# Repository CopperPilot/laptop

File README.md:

# CopperPilot Laptop

**A 13-inch, 13.5 mm thin aluminium laptop built around a Raspberry Pi Compute Module 5, with a 66 Wh 2S battery, 20 V USB-C charging, a scissor keyboard, a glass trackpad and a webcam. Designed end to end by CopperPilot.**

> [!NOTE]
> **Designed by [CopperPilot](https://copperpilot.ai).** CopperPilot's agents designed every board, schematic, layout and enclosure part in this repo from one prompt and a few reference photos, then checked them with the gates and reviews below. Nobody edited the design files by hand: the owner gave plain-English feedback between runs (it is at the end of the prompt), and the agents made every change. **It has not been fabricated, assembled or powered on yet.** Everything here is open for review: if you see something a senior engineer would flag, [open an issue](../../issues/new/choose).

The main board is a carrier for the Compute Module 5 that runs the keyboard, trackpad, display, webcam, speakers,
battery charging and power. Two small daughter boards sit at the edges: two USB-C ports on the left (one is the
20 V charging input) and the headphone jack and microphone on the right. Flat cables join everything, including the
display and webcam cables, which pass through a barrel between the two torque hinges.

## Status

### Done

- [x] Schematic: KiCad ERC, 0 errors
- [x] Layout: KiCad DRC with schematic parity and zone refill, 0 errors, 0 unconnected
- [x] Board rules no looser than the fab's limits, nothing silenced
- [x] Every part on the footprint and 3D model of its exact LCSC part
- [x] Every placed part has a live, in-stock LCSC/JLCPCB part number
- [x] High-speed groups (USB, MIPI, DDR where present) routed, length-matched, on target impedance
- [x] Every user-facing connector opens towards its case opening (checked on its 3D model)
- [x] Every connector mates from a known side, with a keep-clear zone KiCad DRC enforces
- [x] Both ends of every board-to-board cable carry the same signal on each wire
- [x] Datasheet-level design review: 0 P0 and 0 P1 findings open on every board
- [x] Enclosure parts are closed solids that fit the product envelope
- [x] Every enclosure part is manufacturable by its process (wall thickness, build size)
- [x] Full assembly with the real PCBAs: no collisions, seated or along any insertion path
- [x] Every cable joins two real connectors and fits its route in every pose
- [x] Every connector faces what mates with it; every screw hole sits on a boss
- [x] Every port opening has its connector right behind it
- [x] Every button and control physically reaches the switch it works
- [x] Every camera's whole field of view clears the case
- [x] Every part is held by something real (screw, snap, clip, adhesive, press fit)
- [x] Gerbers, drill, BOM and CPL exist and agree with the PCB
- [x] Independent judge (compares renders to the reference photos): **8/10** ([notes](reviews/judge.md))

### Pending

- [ ] Gate `sourcing.bom` warn: 84 extended parts (each adds a JLCPCB feeder fee); prefer basic parts where equivalent
- [ ] Gate `kicad.drc` warn: [main] DRC warning lib_footprint_mismatch x82
- [ ] **Not built.** No board has been fabricated, assembled or powered on, and the enclosure has not been machined.
- [ ] **No software bring-up.** The CM5 device tree, keyboard matrix (TCA8418), trackpad, display panel, webcam and charger settings over I2C are not written or tested.
- [ ] **Bought parts are specified from drawings.** The keyboard, trackpad, 13-inch MIPI panel, hinges, speakers and the custom 2S2P pack are modelled from typical drawings; real suppliers and exact parts still have to be chosen and the models checked against them.
- [ ] **Thermal design not analysed.** No thermal simulation or heat-spreading plan for the CM5 inside the closed aluminium case.
- [ ] **Peak battery current to verify.** Several earlier design reviews estimated that peak load near the 2S cut-off (CM5, display, speakers and USB-C together) can exceed the BQ25798's 6 A internal battery switch; the final review did not raise it. Measure the peak load budget at bring-up, and add an external battery switch or a load cap if it holds.
- [ ] **Thickness:** the assembly measures 13.45 mm against the 12.7 mm target (within the ±1 mm tolerance the design contract allows).
- [ ] **Judge notes (8/10):** separate left and right torque-hinge barrels with a centre cable cover, where the reference has one full-width clutch cover; full-height arrow keys instead of a half-height inverted-T cluster; the webcam window is a rectangular cutout rather than a flush glass hole.
- [ ] **DRC warnings:** 245 across the boards (mostly footprints that differ from their library copy and silkscreen over copper or overlapping); 0 errors.

0 P0 · 0 P1 · 0 P2 review findings open; the full reviews with evidence and suggested fixes are in [reviews/](reviews). Every P0 and P1 the reviews raised was fixed before release.

## Build film

[docs/build-film.mp4](docs/build-film.mp4) (51 s, 720p). Every part backs out along the direction it was fitted and goes back in assembly order, and every cable is drawn along its real route. Every frame is replayed against the 3D models (no part passes through another, the camera stays outside, the product stays in frame and faces you, no flicker), and a separate critic watches the film ([notes](reviews/film.md)).

## Renders

| | |
|:---:|:---:|
| <br>*Three-quarter view* | <br>*Front* |
| <br>*Rear* | <br>*Left side* |
| <br>*Right side* | <br>*Exploded* |
| <br>*Inside, top cover lifted away, every cable* | <br>*Inside from below, bottom cover lifted away* |
| <br>*Ports* | <br>*Buttons and controls, next to the parts they press* |

## What's inside

**Power path:** USB-C PD sink (CH224A, asks for 20 V) → BQ25798 buck-boost charger with NVDC power path → one
2S2P pack of four identical LP4466104 cells (7.4 V, 9 Ah, 66.6 Wh) shaped around the trackpad → two 6 A 5 V bucks
(TPS56628) for the CM5 and the peripherals.

| Board | Size | Layers | Parts | Tracks | Vias | KiCad project | Review |
|---|---|---|---|---|---|---|---|
| Main board | 160 × 44 mm | 4 | 285 | 5,693 | 856 | [`hardware/thin-laptop-cm5.kicad_pro`](hardware/thin-laptop-cm5.kicad_pro) | [0 P0 · 0 P1](reviews/review-main.md) |
| Left Dual USB-C PD & Data Daughter Board | 36 × 38 mm | 4 | 67 | 1,218 | 93 | [`hardware/usb_left/thin-laptop-cm5-usb_left.kicad_pro`](hardware/usb_left/thin-laptop-cm5-usb_left.kicad_pro) | [0 P0 · 0 P1](reviews/review-usb_left.md) |
| Right Headphone & Microphone Daughter Board | 36 × 38 mm | 2 | 74 | 555 | 84 | [`hardware/audio_right/thin-laptop-cm5-audio_right.kicad_pro`](hardware/audio_right/thin-laptop-cm5-audio_right.kicad_pro) | [0 P0 · 0 P1](reviews/review-audio_right.md) |

**Bought parts** (modelled from their drawings; the assembly checks use these models):

- **Cm5 module**: Raspberry Pi Compute Module 5 (BCM2712 quad-core Cortex-A76, 8GB LPDDR4X, 64GB eMMC, Wi-Fi/BLE)
- **Keyboard module**: 78-key ANSI ultra-thin scissor-switch laptop keyboard module with printed legends and 24-pin 0.5mm FPC tail
- **Trackpad module**: Capacitive multi-touch glass-surface I2C laptop trackpad module with 8-pin 0.5mm FPC tail
- **Display panel**: 13.0-inch 2560x1600 4-lane MIPI DSI IPS thin LCD panel with integrated WLED backlight bar
- **Webcam module**: Slim 1080p MIPI CSI-2 camera module with 22-pin 0.5mm micro-coax receptacle for laptop top bezel
- **Battery pack**: Custom 2S2P 7.4V nominal
- **Speaker left**: Low-profile 8-ohm 2W rectangular laptop speaker box module (left channel)
- **Speaker right**: Low-profile 8-ohm 2W rectangular laptop speaker box module (right channel)
- **Hinge left**: Compact friction torque laptop hinge (left)
- **Hinge right**: Compact friction torque laptop hinge (right)

## How it was made

CopperPilot's agents worked from the prompt in [reference/prompt.md](reference/prompt.md) and 6 reference photos ([reference/](reference)). The pipeline scopes the product into a written contract ([design/spec.yaml](design/spec.yaml)), designs the boards and the enclosure in parallel, integrates them, and only moves on when the gates pass. A separate review agent reads every board against the part datasheets, and a separate judge compares the result with the photos.

- Pipeline wall clock: about **136 h** over 25 launches (pipeline v68 to v127).

**Reference vs build:**

<sub>Reference photos of a commercial product, used here only for comparison. All rights belong to their owners; this project is not affiliated with or endorsed by the product's maker.</sub>

## Repository layout

```
hardware/          KiCad 10 projects (main board at the top, daughter boards in their own folders)
  lcsc.*, rea_refs.*   symbols, footprints and 3D models for every part, so the project opens anywhere
case/out/          enclosure parts (STL)
case/purchased/    bought parts used in the assembly checks
case/generate_case.py  the parametric enclosure source (uses CopperPilot's CAD helpers, not yet public)
fab/               Gerbers, drill, BOM, CPL, schematic PDF and STEP for each board; fab/mech/ enclosure STEP/STL
design/spec.yaml   the design contract the agents wrote and the gates check
reviews/           gate report, design reviews, the judge's notes, KiCad ERC/DRC
reference/         the prompt and the reference photos
docs/              build film and renders
```

## Manufacture

Every board targets **JLCPCB** standard PCB + assembly (1.6 mm FR-4); every part has an LCSC number. Per board: upload `*-gerbers.zip`, then `*-bom.csv` and `*-cpl.csv` for assembly, and check the part rotations in JLCPCB's preview before ordering.

The enclosure (`fab/mech/`) is designed for CNC-machined 6061 aluminium; STEP files are included for machining
quotes, STLs for test prints.

> [!WARNING]
> This design has not been built yet. Fix or accept the open review findings above before you order boards, and expect a first revision to need changes.

## Review this design

Hardware gets better with more eyes on it. We'd like to hear what you'd flag:

- **Open an issue** ([design review template](../../issues/new/choose)) for a wrong pin, a missing part, a tight clearance, a part you'd swap, or a P1 above you disagree with.
- **Send a pull request** with a fix. Say which board and which reference designators it touches.
- **Build one** and tell us how it went: photos, bring-up notes and failures are all welcome.

Start with [reviews/](reviews): every finding has its evidence and a suggested fix.

## License

[CERN-OHL-S-2.0](LICENSE). You may use, study, modify, make and sell products from this design; modified versions must be shared under the same licence.

Bought-part names and the Raspberry Pi Compute Module are named only to say what fits; all trademarks belong to their owners.

<p align="center"><a href="https://copperpilot.ai"><b>Designed by CopperPilot</b></a>: we accelerate hardware design.<br><sub>More open designs: <a href="https://github.com/CopperPilot">github.com/CopperPilot</a></sub></p>

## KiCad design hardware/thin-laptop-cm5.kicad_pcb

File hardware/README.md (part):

# 13-inch Thin Aluminum CM5 Laptop — Hardware Design & Verification (`hardware/README.md`)

Generated from `rea/spec.yaml` and completed for the main carrier PCB (`hardware/thin-laptop-cm5`) and inter-board interfaces (`c_usb_left` and `c_audio_right`). Every placed BOM symbol carries a verified in-stock `LCSC` part number.

---

## 1. Inter-Board Cable Pinouts (`board.cable_pinout` 1:1 Straight Convention)

Both board-to-board FFC cables (`c_usb_left` and `c_audio_right`) and high-current wire-to-board harnesses (`J4`, `J5`) use a **1:1 straight pin-number mapping** (`Pin k` on `main` connects to `Pin k` on the sub-board with identical net semantics).

### 1.1 `c_usb_left`: Main Board `J_USBL` (`05B20U16P`, `C18164516`) <-> Left USB-C Board `J3` (`FPC-05F-16PH20`, `C2856801`) + High-Current Harnesses `J4` & `J5`

- **16-pin 0.5mm Type-B (Opposite-Side / Reversed-Contact) FFC (`c_usb_left`, `J_USBL` top-contact `05B20U16P` `C18164516` <-> `J3` bottom-contact `FPC-05F-16PH20` `C2856801`):**
  - Pins 1..4, 7..8 are protected on `main` by two 5-channel 3.3V ESD TVS arrays `D29` and `D30` (`2x PESD3V3L5UY`, `C2831531`, SOT-363):
    - Pin 1 `/USBL_PD_PG_N` (`U1.10 PG` via non-inverting 2-stage `2N7002` open-drain buffer `Q3` + `Q6` with `R5 = 10k`, `R24 = 100k` to `/PD_VDD_3V3`, and `R25` removed on `usb_left`) -> CM5 `GPIO9` (`U1` pin 40, pulled up exclusively via `R75 = 10k` to `/+3V3`)
    - Pin 2 `/USBL_U3_FLT_N` (`U3.9 ~FLT` via non-inverting 2-stage `2N7002` open-drain buffer `Q5` + `Q7` with `R6 = 10k`, `R23 = 100k` to `/PD_VDD_3V3`, and `R26` removed on `usb_left`) -> CM5 `GPIO10` (`U1` pin 44, pulled up exclusively via `R76 = 10k` to `/+3V3`)
    - Pin 3 `/USBL_U5_FLT_N` (`U5.9 ~FLT`, with `R7` removed on `usb_left`) -> CM5 `GPIO26` (`U1` pin 24, pulled up exclusively via `R77 = 10k` to `/+3V3`)
    - Pin 4 `/USBL_J1_FAULT_N` (`U2.1 ~FAULT`, with `R9` removed on `usb_left`) -> CM5 `GPIO6` (`U1` pin 30, pulled up exclusively via `R78 = 10k` to `/+3V3`)
  - Pins 5, 6: `GND` (Ground return)
  - Pins 7, 8:
    - Pin 7 `/USBL_J1_UFP_N` (`U2.19 ~UFP`, with `R10` removed on `usb_left`) -> CM5 `GPIO25` (`U1` pin 41, pulled up exclusively via `R79 = 10k` to `/+3V3`)
    - Pin 8 `/USBL_J1_EN` (`U2.6 EN` on `usb_left` `TPS25810RVCR` with local `R8 = 100 kOhm` pull-down to `/GND` + main-board `U_VBUS.4 EN` with `R8 = 100 kOhm` `C25741` pull-down to `/GND`) <- CM5 `VBUS_EN` (`U1` pin 111, `/CM5_VBUS_EN`) via `R91 = 10 kOhm` (`C25744`) series resistor, gated low below `V_THROT_FALL = 7.160V typ / 7.060V min` `/VSYS` (`V_THROT_RISE = 7.582V typ / 7.487V min`, `422mV` hysteresis via co-located `R88 = 80.6k` `0402WGF8062TCE` `C25798` / `R89 = 4.7k` `0402WGF4701TCE` `C25900` + `R97 = 100k` `C25741` / `Q6` `BSS138` `C52895` on `U_UVLO.4` `INB-` `/VSYS_THROT`) by low-battery load-shedding N-MOSFET `Q5` (`BSS138` `C52895`) driven by `U_UVLO` `OUTB` (`/VBUS_ISET_HI`, pulled up to `/+3V3` via `R90 = 47 kOhm` `0402WGF4702TCE` `C25792`)
  - Pin 9: `GND` (High-speed reference ground flanking `USB3-0` pair)
  - Pins 10 / 11: `USB3-0-D_P` (U1 pin 134) / `USB3-0-D_N` (U1 pin 136) <-> Front-left USB-C `J2` D+/D- (protected on `main` by `U_ESD1` `USBLC6-2SC6` with Pin 5 `VBUS` isolated onto dedicated local `100nF` capacitor `C90` `C307331` `/ESD1_VBUS` to `/GND` per ST `USBLC6-2SC6` Figure 4 so only the internal central Zener rail clamp is used without back-powering `/+5V_PER`)
  - Pin 12: `GND` (High-speed isolation ground between `USB3-0` and `USB3-1` differential pairs)
  - Pins 13 / 14: `USB3-1-D_P` (U1 pin 163) / `USB3-1-D_N` (U1 pin 165) <-> Rear-left USB-C `J1` D+/D- (protected on `main` by `U_ESD2` `USBLC6-2SC6` with Pin 5 `VBUS` isolated onto dedicated local `100nF` capacitor `C91` `C307331` `/ESD2_VBUS` to `/GND` per ST `USBLC6-2SC6` Figure 4 so only the internal central Zener rail clamp is used without back-powering `/+5V_PER`)
  - Pins 15, 16, 17, 18: `GND` (Return and grounded mechanical shell tabs)
- **10-pin 1.0mm Wire-to-Board Charging Harness (`J5` `SM10B-SRSS-TB(LF)(SN)`, `C160409`):**
  - Pins 1..5: `VBUS_PD` (5 x 1.0A = 5.0A rating > 2.25A hardware-capped 20V PD current [45W], clamped at `J5` by low-clamping 22V-standoff / 27.7V-clamping surge TVS `D7` `TVS2200DRVR` `C2875234` and switched into `U_CHG` `/CHG_VBUS` via back-to-back 40V N-MOSFETs `Q3`/`Q4` `2x SQ2318AES-T1_BE3` `C2847989` driven by `U_CHG` `ACDRV1`)
  - Pins 6..10, 11, 12: `GND` (5.0A continuous return + grounded shell tabs)
- **6-pin 1.0mm Wire-to-Board Accessory VBUS Harness (`J4` `SM06B-SRSS-TB(LF)(SN)`, `C160405`):**
  - Pins 1..3: `+5V_USBC` (3 x 1.0A = 3.0A continuous rating, switched from the 6A `/+5V_PER` synchronous buck rail `U_BUCK2` `TPS56628DDAR` by `U_VBUS` `SY6280AAC` `C55136` with fixed `R31 = 3.6 kOhm` 1% `C25891` on `/USB_ISET` setting `I_LIM = 1.89 A typ <= 2.0 A` continuous rating [matching `usb_left`'s `1.5 A` `TPS25810RVCR` Type-C Rp contract with zero current-limit mismatch] and `EN` synchronized with `usb_left` `TPS25810RVCR` `EN` on `/USBL_J1_EN` so both `U_VBUS` and the `1.5 A` Type-C Rp advertisement cleanly shed below `V_THROT_FALL = 7.160 V typ / 7.060 V min` `/VSYS` [`V_THROT_RISE = 7.582 V typ / 7.487 V min`, `422 mV` hysteresis via co-located `R88 = 80.6k` `0402WGF8062TCE` `C25798` / `R89 = 4.7k` `0402WGF4701TCE` `C25900` + `R97 = 100k` `C25741` / `Q6` `BSS138` `C52895` on `U_UVLO.4` `INB-`], keeping worst-case 2S battery discharge current `<= 5.35 A <= 6.0 A` continuous `BQ25798RQMR` internal BATFET rating down to `V_UVLO_FALL = 6.610 V`, decoupled by `C19 = 10uF` and clamped by unidirectional 5.0V low-clamping TVS `D2` `PSD05-LF-T7` `C139296`)
  - Pins 4..6, 7, 8: `GND` (3.0A continuous return + grounded shell tabs)

### 1.2 `c_audio_right`: Main Board `J_AUDR` (`FPC-05F-8PH20`, `C2856797`) <-> Right Audio Board `J2` (`FPC-05FB-8PH20`, `C2856828`)

- Pin 1: `GND` (Analog/headphone ground return)
- Pin 2: `HP_L` (`main -> audio_right`, AC-coupled Left headphone output via `C29 + C52 = 200uF` and `R61 = 10R` with `D10` `PESD5V0S1BA` ESD clamp)
- Pin 3: `HP_R` (`main -> audio_right`, AC-coupled Right headphone output via `C30 + C53 = 200uF` and `R62 = 10R` with `D11` `PESD5V0S1BA` ESD clamp)
- Pin 4: `GND` (Guard ground isolating headphone outputs from differential microphone inputs)
- Pin 5: `MIC_P` (`audio_right -> main`, differential microphone positive to `ES8388` `LIN1` via `C33 = 2.2uF` with symmetrical DC charge bleeder `R51 = 47k` `C25792` to `/GND` and `D12` `PESD5V0S1BA` ESD clamp)
- Pin 6: `MIC_N` (`audio_right -> main`, differential microphone negative to `ES8388` `RIN1` via `C34 = 2.2uF` with symmetrical DC charge bleeder `R52 = 47k` `C25792` to `/GND` and `D13` `PESD5V0S1BA` ESD clamp)
- Pin 7: `HP_DET` (`audio_right -> main`, active-low headphone plug detect from `TLV7041DBVR` on `audio_right`, routed to CM5 `GPIO24` `U1` pin 45 with `R37 = 10k` pull-up to `+3V3` and unidirectional 3.3V ESD diode `D14` `PESD3V3U1UA,115` `C403915`, isolated from main-board `/LID_SNS` on `GPIO13` `U1` pin 28)
- Pin 8: `+3V3_PER` (`main -> audio_right`, switched and current-limited +3.3V peripheral rail fed directly from `U_3V3` `TLV62569DBVR` `/+3V3_PER` with `F5` removed, locally decoupled by `C38 = 100nF` and clamped by 3.3V ESD TVS diode `D32` `PESD3V3U1UA,115` `C403915`)
- Pins 9, 10: `GND` (Mechanical shell tabs grounded)

---

## 2. Peripheral Connector Pinouts on Main Board

### 2.1 `J_DSI` (MIPI DSI1 22-pin 0.5mm FFC `FH12-22S-0.5SH(55)`, `C597981`) — Raspberry Pi 22-Way Standard
- Pins 1, 4, 7, 10, 13, 16, 19, 23, 24: `GND`
- Pins 2 / 3: `MIPI1_D0_N` (U1 pin 175) / `MIPI1_D0_P` (U1 pin 177)
- Pins 5 / 6: `MIPI1_D1_N` (U1 pin 181) / `MIPI1_D1_P` (U1 pin 183)
- Pins 8 / 9: `MIPI1_C_N` (U1 pin 187) / `MIPI1_C_P` (U1 pin 189)
- Pins 11 / 12: `MIPI1_D2_N` (U1 pin 193) / `MIPI1_D2_P` (U1 pin 195)
- Pins 14 / 15: `MIPI1_D3_N` (U1 pin 194) / `MIPI1_D3_P` (U1 pin 196)
- Pins 17 / 18: `DSI_RST_N` (U1 `GPIO7` pin 37 + `R55 = 10k` pull-down) / `DSI_EN` (U1 `GPIO8` pin 39 + `R56 = 10k` pull-down)
- Pins 20 / 21: `SCL0_PER` / `SDA0_PER` (isolated via `Q_I2C1`/`Q_I2C2` `BSS138` from U1 pins 80/82, pulled up via `R9 = 2.2k` `C25879` / `R10 = 2.2k` `C25879` to switched `+3V3_PER`)
- Pin 22: `+3V3_PER` (fed directly from low-impedance switched/current-limited `/+3V3_PER` buck rail `U_3V3` `TLV62569DBVR` with `F2` removed to eliminate PTC IR drop, locally decoupled by `C45 = 10uF` and `C46 = 100nF`; pins 17, 18, 20, 21, 22 are ESD-protected at `J_DSI` by 5-channel 3.3V SOT-363 TVS array `D33` `PESD3V3L5UY` `C2831531`)

### 2.2 `J_CSI` (MIPI CSI0 22-pin 0.5mm FFC `FH12-22S-0.5SH(55)`, `C597981`) — Raspberry Pi 22-Way Standard
- Pins 1, 4, 7, 10, 13, 16, 19, 23, 24: `GND`
- Pins 2 / 3: `MIPI0_D0_N` (U1 pin 115) / `MIPI0_D0_P` (U1 pin 117)
- Pins 5 / 6: `MIPI0_D1_N` (U1 pin 121) / `MIPI0_D1_P` (U1 pin 123)
- Pins 8 / 9: `MIPI0_C_N` (U1 pin 127) / `MIPI0_C_P` (U1 pin 129)
- Pins 11..15: Unconnected (`no_connect`, 2-lane CSI0 camera interface)
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
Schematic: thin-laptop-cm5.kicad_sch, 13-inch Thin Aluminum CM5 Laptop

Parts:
C1, C3, C9, C19, C24, C35, C41, C43, C45, C47, C49, C65, C66, C67, C69, C71, C72, C73, C74, C75, C99: 10uF; C_0805_2012Metric; LCSC C440198
C2, C4, C10, C12, C16, C18, C23, C25, C36, C38, C42, C44, C46, C48, C50, C54, C59, C68, C76, C77, C80, C83, C87, C90, C91, C93, C96, C101: 100nF; C_0402_1005Metric; LCSC C307331
C5, C6, C14, C15, C55, C56, C64, C81, C82, C84, C85, C86: 22uF; C_0805_2012Metric; LCSC C45783
C7, C13: 47nF; C_0402_1005Metric; LCSC C880605
C8, C51, C88: 4.7uF; C_0603_1608Metric; LCSC C19666
C11, C31, C32, C79: 1uF; C_0402_1005Metric; LCSC C52923
C17, C78: 22pF; C_0402_1005Metric; LCSC C1555
C20: 10uF; C_0603_1608Metric; LCSC C96446
C21: 220nF; C_0402_1005Metric; LCSC C16772
C22: 1uF; C_0603_1608Metric; LCSC C23829972
C26, C27, C28, C37, C39, C40, C57, C58: 1uF; C_0603_1608Metric; LCSC C15849
C29, C30, C52, C53: 100uF; C_0805_2012Metric; LCSC C141660
C33, C34: 2.2uF; C_0402_1005Metric; LCSC C159814
C60, C61, C62, C63: 1nF; C_0402_1005Metric; LCSC C1523
C70: 1nF; C_0402_1005Metric; LCSC C14442
C89: 470pF; C_0402_1005Metric; LCSC C1537
C92: 10nF; C_0402_1005Metric; LCSC C15195
C95, C97: 100nF; C_0402_1005Metric; MPN CC0402KRX7R9BB104; LCSC C307331
C98: 10nF; C_0402_1005Metric; MPN CL05B103KB5NNNC; LCSC C15195
C100: 220nF; C_0402_1005Metric; MPN CL05B224KO5NNNC; LCSC C16772
D1: B16WS; SOD-323_L1.8-W1.3-LS2.5-RD; LCSC C364278
D2, D18: PSD05-LF-T7; SOD-323_L1.8-W1.3-LS2.5-RD; LCSC C139296
D3: TSD05CDYFR; SOD-323_L1.8-W1.3-LS2.5-BI; LCSC C20611048
D4, D6, D9, D19: PESD5V0S1UA,115; SOD-323_L1.8-W1.3-LS2.5-RD; LCSC C179414
D5, D14: PESD3V3U1UA,115; SOD-323_L1.7-W1.3-LS2.5-RD; LCSC C403915
D7: ESTVS2200DRVR; DFN-6_L2.0-W2.0-P0.65-BL-EP1.6; LCSC C42400188
D10, D11, D12, D13: PESD5V0S1BA; SOD-323_L1.7-W1.3-LS2.5-BI; LCSC C2827694
D15: BZT52C12; SOD-123_L2.7-W1.6-LS3.7-RD; LCSC C173429
D16: 1N4148WS; SOD-323_L1.8-W1.3-LS2.5-RD; LCSC C2128
D20, D21, D22, D23, D31, D32, D40: PESD3V3U1UA,115; SOD-323_L1.7-W1.3-LS2.5-RD; MPN PESD3V3U1UA,115; LCSC C403915
D24: SMF12A; SOD-123F_L2.8-W1.8-LS3.7-RD; MPN SMF12A; LCSC C123800
D25, D26, D27, D28, D29, D30: PESD3V3L5UY; SOT-363_L2.0-W1.3-P0.65-LS2.1-BL; MPN PESD3V3L5UY; LCSC C2831531
D33, D34: PESD3V3L5UY; SOT-363_L2.0-W1.3-P0.65-LS2.1-BL; LCSC C2831531
D35: ESTVS3300DRVR; DFN-6_L2.0-W2.0-P0.65-BL-EP1.6; LCSC C42400190
D36: PESD36VS1UJX; SOD-323F_L1.7-W1.3-LS2.5-RD; LCSC C5205187
D37, D39: 1N4148WS; SOD-323_L1.8-W1.3-LS2.5-RD; MPN 1N4148WS; LCSC C2128
D38: BZT52C5V1S; SOD-323_L1.8-W1.3-LS2.5-RD; LCSC C173436
F1: 8A; F1206; LCSC C136353
F6: 1A; F0603; LCSC C163118
FB1, FB2, FB3, FB4, FB5: BLM18PG121SN1D; L0603; LCSC C14709
H1, H2, H3, H4: MountingHole_2.2mm_M2
J4: SM06B-SRSS-TB(LF)(SN); CONN-SMD_SM06B-SRSS-TB-LF-SN; LCSC C160405
J5: SM10B-SRSS-TB(LF)(SN); CONN-SMD_10P-P1.00_SM10B-SRSS-TB-LF-SN; LCSC C160409
J_AUDR: FPC-05F-8PH20; FPC-SMD_8P-P0.50_FPC-05F-8PH20; LCSC C2856797
J_BAT: S9B-PH-SM4-TB(LF)(SN); CONN-SMD_9P-P2.50_S9B-PH-SM4-TB; MPN S9B-PH-SM4-TB(LF)(SN); LCSC C495694
J_BL: S2B-PH-SM4-TB(LF)(SN); CONN-SMD_P2.00_S2B-PH-SM4-TB-LF-SN; LCSC C295747
J_CSI: FH12-22S-0.5SH(55); FPC-SMD_22P-P0.50_FH12-22S-0.5SH-55; LCSC C597981
J_DSI: FH12-22S-0.5SH(55); FPC-SMD_22P-P0.50_FH12-22S-0.5SH-55; LCSC C597981
J_KB: 05A20L24P; FPC-SMD_24P-P0.50_05A20L24P; LCSC C5362158
J_SPKL: S2B-PH-SM4-TB(LF)(SN); CONN-SMD_P2.00_S2B-PH-SM4-TB-LF-SN; LCSC C295747
J_SPKR: S2B-PH-SM4-TB(LF)(SN); CONN-SMD_P2.00_S2B-PH-SM4-TB-LF-SN; LCSC C295747
J_TP: FPC-05F-8PH20; FPC-SMD_8P-P0.50_FPC-05F-8PH20; LCSC C2856797
J_USBL: 05B20U16P; FPC-SMD_16P-P0.50_05B20U16P; LCSC C18164516
L1, L2, L5: 2.2uH; IND-SMD_L7.0-W6.6; LCSC C167218
L3: 10uH; IND-SMD_L4.0-W4.0_LQH44PN2R2MP0L; LCSC C135263
L4: 2.2uH; IND-SMD_L4.5-W4.1_TMPC0412HP; MPN TMPC0402HP-2R2MG-Z02; LCSC C357134
Q1, Q2: AO4407A; SOP-8_L5.0-W4.0-P1.27-LS6.0-BL; LCSC C2841482
Q3, Q4: SQ2318AES-T1_BE3; SOT-23-3_L2.9-W1.3-P1.90-LS2.4-BR; LCSC C3280170
Q5, Q6: BSS138; SOT-23-3_L2.9-W1.6-P1.90-LS2.8-BR; LCSC C52895
Q_BL: AO3401A; SOT-23_L2.9-W1.3-P1.90-LS2.4-BR; LCSC C15127
Q_BL_EN: 2N7002; SOT-23-3_L2.9-W1.3-P1.90-LS2.4-BR; LCSC C8545
Q_CAM: BSS138; SOT-23-3_L2.9-W1.6-P1.90-LS2.8-BR; LCSC C52895
Q_DBG: 2N7002; SOT-23-3_L2.9-W1.3-P1.90-LS2.4-BR; LCSC C8545
Q_I2C1, Q_I2C2: BSS138; SOT-23-3_L2.9-W1.6-P1.90-LS2.8-BR; LCSC C52895
Q_TP1, Q_TP2: BSS138; SOT-23-3_L2.9-W1.6-P1.90-LS2.8-BR; LCSC C52895
R1, R2, R3, R4, R6, R13, R14, R15, R16, R17, R18, R19, R20, R21, R26, R37, R48, R54, R55, R56, R58, R59, R71, R75, R76, R77, R78, R79, R91, R93: 10k; R_0402_1005Metric; LCSC C25744
R7: 30k; R_0402_1005Metric; LCSC C25776
R8, R30, R35, R45, R46, R63, R66, R67, R80: 100k; R_0402_1005Metric; LCSC C25741
R9, R10: 2.2k; R_0402_1005Metric; LCSC C25879
R22: 8.2k; R_0603_1608Metric; LCSC C25981
R23: 5.23k; R_0402_1005Metric; LCSC C11631
R27: 137k; R_0402_1005Metric; LCSC C32298
R28, R65: 24k; R_0402_1005Metric; LCSC C25769
R29: 78.7k; R_0402_1005Metric; LCSC C2998104
R31: 3.6k; R_0402_1005Metric; MPN 0402WGF3601TCE; LCSC C25891
R32: 1.5R; R_0603_1608Metric; LCSC C22769
R33: 82k; R_0402_1005Metric; LCSC C4142
R34: 5.1k; R_0402_1005Metric; LCSC C25905
R36, R53: 22R; R_0402_1005Metric; LCSC C25092
R42: 30.1k; R_0402_1005Metric; LCSC C29402
R47: 45.3k; R_0402_1005Metric; LCSC C26980
R49: 4.7R; R_0402_1005Metric; LCSC C25121
R50, R69: 100R; R_0402_1005Metric; LCSC C25076
R51, R52, R90: 47k; R_0402_1005Metric; MPN 0402WGF4702TCE; LCSC C25792
R60: 2.2R; R_0603_1608Metric; LCSC C22939
R61, R62, R74: 10R; R_0402_1005Metric; LCSC C25077
R64: 133k; R_0402_1005Metric; LCSC C25753
R68: 47k; R_0402_1005Metric; LCSC C25792
R72, R73: 150k; R_0402_1005Metric; LCSC C25755
R81: 1M; R_0402_1005Metric; LCSC C26083
R82, R83: 2.2k; R_0402_1005Metric; MPN 0402WGF2201TCE; LCSC C25879
R84: 1k; R_0402_1005Metric; MPN 0402WGF1001TCE; LCSC C11702
R87: 100R; R_0402_1005Metric; MPN 0402WGF1000TCE; LCSC C25076
R88: 80.6k; R_0402_1005Metric; MPN 0402WGF8062TCE; LCSC C25921
R89: 4.7k; R_0402_1005Metric; MPN 0402WGF4701TCE; LCSC C25900
R94: 22k; R_0402_1005Metric; MPN 0402WGF2202TCE; LCSC C25768
R95: 10k; R_0402_1005Metric; MPN 0402WGF1002TCE; LCSC C25744
R96, R97: 100k; R_0402_1005Metric; MPN 0402WGF1003TCE; LCSC C25741
SW1: PTS526SM15SMTR2LFS; SW-SMD_4P-L5.2-W5.2-P3.70-LS6.4; LCSC C2689538
TP1: TP1; TestPoint_Pad_D1.5mm
TP2: TP2; TestPoint_Pad_D1.5mm
TP3: TP3; TestPoint_Pad_D1.5mm
TP4: TP4; TestPoint_Pad_D1.5mm
TP5: TP5; TestPoint_Pad_D1.5mm
TP6: TP6; TestPoint_Pad_D1.5mm
U1: ComputeModule5-CM5; Raspberry-Pi-5-Compute-Module; LCSC C597931
U_3V3: TLV62569DBVR; SOT-23-5_L3.0-W1.7-P0.95-LS2.8-BR; MPN TLV62569DBVR; LCSC C141836
U_AMP: PAM8406DR; SOIC-16_L9.9-W3.9-P1.27-LS6.0-BL; LCSC C86270
U_BL: TPS61165DBVR; SOT-23-6_L2.9-W1.6-P0.95-LS2.8-BR; LCSC C58756
U_BUCK, U_BUCK2: TPS56628DDAR; SOIC-8_L4.9-W3.9-P1.27-LS6.0-BL-EP; LCSC C485522
U_CHG: BQ25798RQMR; QFN-29_L4.0-W4.0-P0.40-TL-BQ25792RQMR; LCSC C2876593
U_CODEC: ES8388; QFN-28_L4.0-W4.0-P0.45-BL-EP; LCSC C365736
U_DBG: TPS2117DRLR; SOT-583-8_L2.1-W1.2-P0.50-LS1.6-BL; LCSC C22399676
U_ESD, U_ESD1, U_ESD2: USBLC6-2SC6; SOT-23-6_L2.9-W1.6-P0.95-LS2.8-BL; LCSC C2687116
U_HALL: DRV5032FADBZR; SOT-23-3_L2.9-W1.3-P0.95-LS2.4-BR; LCSC C140921
U_KB: TCA8418RTWR; WQFN-24_L4.0-W4.0-P0.50-TL-EP2.5; LCSC C138713
U_RTC: HT7530S; SOT-23-3_L3.0-W1.7-P0.95-LS2.9-BR; LCSC C347214
U_UVLO: TPS3700DDCR; SOT-23-6_L2.9-W1.6-P0.95-LS2.8-BL; LCSC C33002
U_VBUS: SY6280AAC; SOT-23-5_L3.0-W1.7-P0.95-LS2.8-BL; LCSC C55136

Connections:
/3V3_PER_EN: R45.1, R46.1, U_3V3.1 (EN)
/3V3_PER_FB: R47.2, R48.1, U_3V3.5 (FB)
/3V3_PER_SW: L4.1, U_3V3.3 (SW)
/+3V3: C23.1, C24.1, C25.1, FB5.1, Q_BL_EN.1 (G), R2.2, R3.2, R4.2, R6.2, R13.2, R14.2, R15.2, R20.2, R21.2, R37.2, R49.1, R63.1, R75.2, R76.2, R77.2, R78.2, R79.2, R90.1, U1.78 (GPIO_VREF(1.8v/3.3v_Input)), U1.84 (+3.3v_(Output)), U1.86 (+3.3v_(Output)), U_BUCK2.1 (EN), U_CODEC.2 (DVDD), U_CODEC.3 (PVDD), U_HALL.1 (VCC), U_KB.21 (VCC)
/+3V3_PER: C38.1, C43.1, C44.1, C45.1, C46.1, C47.1, C48.1, C97.1, C101.1, D31.1, D32.1, D33.6, D34.6, J_AUDR.8, J_CSI.22, J_DSI.22, J_TP.2, L4.2, Q_CAM.1 (G), Q_I2C1.1 (G), Q_I2C2.1 (G), Q_TP1.1 (G), Q_TP2.1 (G), R9.1, R10.1, R18.2, R19.2, R47.1, R82.1, R83.1, R95.1
/+5V: C14.1, C15.1, C16.1, C17.1, C64.1, D3.1, L2.2, Q1.5 (D), Q1.6 (D), Q1.7 (D), Q1.8 (D), R27.1
/+5V_CM5: C54.1, C55.1, C56.1, C98.1, Q2.5 (D), Q2.6 (D), Q2.7 (D), Q2.8 (D), R1.2, U1.77 (+5v_(Input)), U1.79 (+5v_(Input)), U1.81 (+5v_(Input)), U1.83 (+5v_(Input)), U1.85 (+5v_(Input)), U1.87 (+5v_(Input)), U_DBG.2 (VOUT), U_DBG.7 (VOUT)
/+5V_PER: C18.1, C35.1, C36.1, C41.1, C42.1, C78.1, C84.1, C85.1, C86.1, C87.1, D18.1 (K), L5.2, R45.2, R64.1, R71.2, U_3V3.4 (VIN), U_AMP.4 (PVDDL), U_AMP.6 (VDD), U_AMP.13 (PVDDR), U_VBUS.5 (IN)
/+5V_USBC: C19.1, D2.1 (K), J4.1, J4.2, J4.3, U_VBUS.1 (OUT)
/AMP_INL: R72.2, U_AMP.7 (INL)
/AMP_INL_AC: C31.2, R72.1
/AMP_INR: R73.2, U_AMP.10 (INR)
/AMP_INR_AC: C32.2, R73.1
/AMP_MODE: R71.1, U_AMP.9 (MODE)
/AMP_OUTL_N: FB2.1, U_AMP.3 (-OUT_L)
/AMP_OUTL_P: FB1.1, U_AMP.1 (+OUT_L)
/AMP_OUTR_N: FB4.1, U_AMP.14 (-OUT_R)
/AMP_OUTR_P: FB3.1, U_AMP.16 (+OUT_R)
/AMP_SHDN_N: R17.1, U1.29 (GPIO16), U_AMP.5 (~MUTE), U_AMP.12 (~SHDN)
/AMP_VREF: C37.1, U_AMP.8 (VREF)
/BAT_TS: J_BAT.5, R87.1
/BL_COMP: C21.1, U_BL.5 (COMP)
/BL_EN_D: Q_BL_EN.3 (D), R80.2
/BL_FB: D38.1, R93.2, U_BL.6 (FB)
/BL_PWM: R16.1, U1.31 (GPIO12), U_BL.2 (CTRL)
/BL_SW: D1.2, L3.1, U_BL.3 (SW)
/BL_SW_G: C92.2, Q_BL.1 (G), R35.1, R80.1
/BT_NDIS: R3.1, U1.91 (BT_nDisable)
/BUCK2_FB: C78.2, R64.2, R65.1, U_BUCK2.2 (VFB)
/BUCK2_PG: R66.2, U_BUCK2.4 (PG)
/BUCK2_SW: C80.1, L5.1, U_BUCK2.6 (SW)
/BUCK2_VBST: C80.2, U_BUCK2.7 (VBST)
/BUCK2_VREG5: C79.1, R66.1, U_BUCK2.3 (VREG5)
/BUCK_EN: R67.2, R68.1, R81.1, U_BUCK.1 (EN), U_UVLO.1 (OUTA)
/BUCK_FB: C17.2, R27.2, R28.1, U_BUCK.2 (VFB)
/BUCK_PG: Q_DBG.1 (G), R26.2, R58.1, U_BUCK.4 (PG)
/BUCK_SW: C12.1, L2.1, U_BUCK.6 (SW)
/BUCK_VBST: C12.2, U_BUCK.7 (VBST)
/BUCK_VREG5: C11.1, R26.1, U_BUCK.3 (VREG5)
/CAM_GPIO0: D40.1, J_CSI.18, R53.2, R54.1
/CAM_GPIO0_SRC: R53.1, U1.97 (CAM_GPIO0)
/CAM_GPIO1: D34.1, J_CSI.17, Q_CAM.2 (S), R95.2, R96.1
/CAM_GPIO1_CM5: Q_CAM.3 (D), U1.100 (CAM_GPIO1)
/CHG_ACDRV1: R69.1, U_CHG.11 (ACDRV1)
/CHG_ACDRV1_G: C89.1, D15.1 (K), Q3.1 (G), Q4.1 (G), R69.2
/CHG_AC_SRC: C89.2, D15.2 (A), Q3.2 (S), Q4.2 (S)
/CHG_BATP: C4.1, R50.2, U_CHG.18 (BATP)
/CHG_BTST1: C7.2, U_CHG.4 (BTST1)
/CHG_BTST2: C13.2, U_CHG.19 (BTST2)
/CHG_DP_DM: U_CHG.6 (D+), U_CHG.7 (D-)
/CHG_ILIM: R29.2, R30.1, U_CHG.17 (ILIM_HIZ)
/CHG_INT_N: R14.1, U1.34 (GPIO5), U_CHG.21 (~INT)
/CHG_PMID: C9.1, C66.1, C67.1, C68.1, U_CHG.29 (PMID)
/CHG_PROG: R22.1, U_CHG.20 (PROG)
/CHG_REGN: C8.1, R23.1, R29.1, U_CHG.5 (REGN)
/CHG_SDRV: C70.1, U_CHG.24 (SDRV)
/CHG_STAT: R15.1, U_CHG.1 (STAT)
/CHG_SW1: C7.1, L1.1, U_CHG.28 (SW1)
/CHG_SW2: C13.1, L1.2, U_CHG.26 (SW2)
/CHG_TS: C59.1, D19.1 (C), R23.2, R42.1, R87.2, U_CHG.16 (TS)
/CHG_VAC1: C96.1, R74.2, U_CHG.9 (VAC1)
/CHG_VBUS: C1.1, C65.1, C77.1, Q4.3 (D), U_CHG.2 (VBUS), U_CHG.3 (VBUS), U_CHG.8 (VAC2)
/CM5_PWR_BUT: D16.2 (A), U1.92 (PWR_BUT)
/CM5_VBUS_EN: R91.1, U1.111 (VBUS_EN)
/CODEC_ADCVREF: C27.1, U_CODEC.19 (ADCVREF)
/CODEC_AVDD: C49.1, C50.1, R49.2, U_CODEC.17 (AVDD)
/CODEC_HPVDD: C99.1, FB5.2, U_CODEC.16 (HPVDD)
/CODEC_LIN1: C33.1, U_CODEC.24 (LIN1)
/CODEC_LOUT1: C29.1, C52.1, U_CODEC.12 (LOUT1)
/CODEC_LOUT2: C31.1, U_CODEC.15 (LOUT2)
/CODEC_MICBIAS: C51.1, U_CODEC.25 (MICBIAS)
/CODEC_RIN1: C34.1, U_CODEC.23 (RIN1)
/CODEC_ROUT1: C30.1, C53.1, U_CODEC.11 (ROUT1)
/CODEC_ROUT2: C32.1, U_CODEC.14 (ROUT2)
/CODEC_VMID: C28.1, U_CODEC.20 (VMID)
/CODEC_VREF: C26.1, U_CODEC.10 (VREF)
/DBG_EN_D: Q_DBG.3 (D), R84.2
/DBG_GATE: D39.1 (K), Q1.4 (G), Q2.4 (G), R59.1, R84.1
/DBG_MILLER: C98.2, D39.2 (A), R94.2
/DBG_PR1: C100.1, R7.1, R58.2, U_DBG.4 (PR1)
/DBG_PWR: C88.1, D4.1 (C), TP1.1, U_DBG.6 (VIN2)
/DBG_Q_SRC: Q1.1 (S), Q1.2 (S), Q1.3 (S), Q2.1 (S), Q2.2 (S), Q2.3 (S), R59.2, R94.1
/DSI_EN: D33.3, J_DSI.18, R56.1, U1.39 (GPIO8)
/DSI_RST_N: D33.1, J_DSI.17, R55.1, U1.37 (GPIO7)
/ESD1_VBUS: C90.1, U_ESD1.5 (VBUS)
/ESD2_VBUS: C91.1, U_ESD2.5 (VBUS)
/ESD_VBUS: C95.1, U_ESD.5 (VBUS)
/GND: C1.2, C2.2, C3.2, C4.2, C5.2, C6.2, C8.2, C9.2, C10.2, C11.2, C14.2, C15.2, C16.2, C18.2, C19.2, C20.2, C21.2, C22.2, C23.2, C24.2, C25.2, C26.2, C27.2, C28.2, C35.2, C36.2, C37.2, C38.2, C39.2, C40.2, C41.2, C42.2, C43.2, C44.2, C45.2, C46.2, C47.2, C48.2, C49.2, C50.2, C51.2, C54.2, C55.2, C56.2, C57.2, C58.2, C59.2, C60.2, C61.2, C62.2, C63.2, C64.2, C65.2, C66.2, C67.2, C68.2, C69.2, C70.2, C71.2, C72.2, C73.2, C74.2, C75.2, C76.2, C77.2, C79.2, C81.2, C82.2, C83.2, C84.2, C85.2, C86.2, C87.2, C88.2, C90.2, C91.2, C93.2, C95.2, C96.2, C97.2, C99.2, C100.2, C101.2, D2.2 (A), D3.2, D4.2 (A), D5.2, D6.2 (A), D7.1 (GND), D7.2 (GND), D7.3 (GND), D7.7 (EP), D9.2 (A), D10.2, D11.2, D12.2, D13.2, D14.2, D18.2 (A), D19.2 (A), D20.2, D21.2, D22.2, D23.2, D24.2 (A), D25.2, D26.2, D27.2, D28.2, D28.5, D28.6, D29.2, D29.6, D30.2, D30.4, D30.5, D30.6, D31.2, D32.2, D33.2, D34.2, D34.3, D35.1 (GND), D35.2 (GND), D35.3 (GND), D35.7 (GND), D36.2 (A), D38.2, D40.2, J4.4, J4.5, J4.6, J4.7, J4.8, J5.6, J5.7, J5.8, J5.9, J5.10, J5.11, J5.12, J_AUDR.1, J_AUDR.4, J_AUDR.9, J_AUDR.10, J_BAT.6, J_BAT.7, J_BAT.8, J_BAT.9, J_BAT.10, J_BAT.11, J_BL.3, J_BL.4, J_CSI.1, J_CSI.4, J_CSI.7, J_CSI.10, J_CSI.13, J_CSI.16, J_CSI.19, J_CSI.23, J_CSI.24, J_DSI.1, J_DSI.4, J_DSI.7, J_DSI.10, J_DSI.13, J_DSI.16, J_DSI.19, J_DSI.23, J_DSI.24, J_KB.20, J_KB.21, J_KB.22, J_KB.23, J_KB.24, J_KB.25, J_KB.26, J_SPKL.3, J_SPKL.4, J_SPKR.3, J_SPKR.4, J_TP.1, J_TP.7, J_TP.8, J_TP.9, J_TP.10, J_USBL.5, J_USBL.6, J_USBL.9, J_USBL.12, J_USBL.15, J_USBL.16, J_USBL.17, J_USBL.18, Q5.2 (S), Q6.2 (S), Q_BL_EN.2 (S), Q_DBG.2 (S), R7.2, R8.2, R16.2, R17.2, R22.2, R28.2, R30.2, R31.2, R32.2, R34.2, R42.2, R46.2, R48.2, R51.1, R52.2, R54.2, R55.2, R56.2, R63.2, R65.2, R68.2, R89.2, R96.2, SW1.3, SW1.4, TP4.1, U1.1 (GND), U1.2 (GND), U1.7 (GND), U1.8 (GND), U1.13 (GND), U1.14 (GND), U1.22 (GND), U1.23 (GND), U1.32 (GND), U1.33 (GND), U1.42 (GND), U1.43 (GND), U1.52 (GND), U1.53 (GND), U1.59 (GND), U1.60 (GND), U1.65 (GND), U1.66 (GND), U1.71 (GND), U1.74 (GND), U1.98 (GND), U1.107 (GND), U1.108 (GND), U1.113 (GND), U1.114 (GND), U1.119 (GND), U1.120 (GND), U1.125 (GND), U1.126 (GND), U1.131 (GND), U1.132 (GND), U1.137 (GND), U1.138 (GND), U1.144 (GND), U1.150 (GND), U1.155 (GND), U1.156 (GND), U1.161 (GND), U1.162 (GND), U1.167 (GND), U1.168 (GND), U1.173 (GND), U1.174 (GND), U1.179 (GND), U1.180 (GND), U1.185 (GND), U1.186 (GND), U1.191 (GND), U1.192 (GND), U1.197 (GND), U1.198 (GND), U_3V3.2 (GND), U_AMP.2 (PGNDL), U_AMP.11 (GND), U_AMP.15 (PGNDR), U_BL.4 (GND), U_BUCK.5 (GND), U_BUCK.9 (GND), U_BUCK2.5 (GND), U_BUCK2.9 (GND), U_CHG.10 (ACDRV2), U_CHG.13 (~CE), U_CHG.27 (GND), U_CODEC.4 (DGND), U_CODEC.13 (HPGND), U_CODEC.18 (AGND), U_CODEC.26 (CE), U_CODEC.29 (EP), U_DBG.1 (GND), U_DBG.3 (VIN1), U_DBG.5 (MODE), U_ESD.2 (GND), U_ESD1.2 (GND), U_ESD2.2 (GND), U_HALL.3 (GND), U_KB.19 (GND), U_KB.25 (EP), U_RTC.1 (GND), U_UVLO.2 (GND), U_VBUS.2 (GND)
/HP_DET: D14.1, J_AUDR.7, R37.1, U1.45 (GPIO24)
/HP_L: D10.1, J_AUDR.2, R61.2
/HP_L_AC: C29.2, C52.2, R61.1
/HP_R: D11.1, J_AUDR.3, R62.2
/HP_R_AC: C30.2, C53.2, R62.1
/I2C_SCL: Q_TP1.3 (D), U1.56 (GPIO3), U_CHG.14 (SCL), U_CODEC.28 (CCLK), U_KB.23 (SCL)
/I2C_SDA: Q_TP2.3 (D), U1.58 (GPIO2), U_CHG.15 (SDA), U_CODEC.27 (CDATA), U_KB.22 (SDA)
/I2S_BCLK: U1.49 (GPIO18), U_CODEC.5 (SCLK)
/I2S_DIN: U1.27 (GPIO20), U_CODEC.8 (ASDOUT)
/I2S_DOUT: U1.25 (GPIO21), U_CODEC.6 (DSDIN)
/I2S_LRCK: U1.26 (GPIO19), U_CODEC.7 (LRCK)
/I2S_MCLK: R36.2, U_CODEC.1 (MCLK)
/I2S_MCLK_SRC: R36.1, U1.54 (GPIO4)
/KB_COL0: D26.5, J_KB.9, U_KB.9 (COL0)
/KB_COL1: D26.6, J_KB.10, U_KB.10 (COL1)
/KB_COL2: D27.1, J_KB.11, U_KB.11 (COL2)
/KB_COL3: D27.3, J_KB.12, U_KB.12 (COL3)
/KB_COL4: D27.4, J_KB.13, U_KB.13 (COL4)
/KB_COL5: D27.5, J_KB.14, U_KB.14 (COL5)
/KB_COL6: D27.6, J_KB.15, U_KB.15 (COL6)
/KB_COL7: D28.1, J_KB.16, U_KB.16 (COL7)
/KB_COL8: D28.3, J_KB.17, U_KB.17 (COL8)
/KB_COL9: D28.4, J_KB.18, U_KB.18 (COL9)
/KB_INT_N: R20.1, U1.46 (GPIO22), U_KB.24 (~INT)
/KB_ROW0: D25.1, J_KB.1, U_KB.8 (ROW0)
/KB_ROW1: D25.3, J_KB.2, U_KB.7 (ROW1)
/KB_ROW2: D25.4, J_KB.3, U_KB.6 (ROW2)
/KB_ROW3: D25.5, J_KB.4, U_KB.5 (ROW3)
/KB_ROW4: D25.6, J_KB.5, U_KB.4 (ROW4)
/KB_ROW5: D26.1, J_KB.6, U_KB.3 (ROW5)
/KB_ROW6: D26.3, J_KB.7, U_KB.2 (ROW6)
/KB_ROW7: D26.4, J_KB.8, U_KB.1 (ROW7)
/KB_RST_N: R21.1, U1.47 (GPIO23), U_KB.20 (~RESET)
/LED_ANODE: C22.1, D1.1, D35.4 (VDD/IO), D35.5 (VDD/IO), D35.6 (VDD/IO), J_BL.1
/LED_CATHODE: D36.1 (C), J_BL.2, R32.1, R93.1
/LID_SNS: R13.1, U1.28 (GPIO13), U_HALL.2 (OUT)
/MIC_N: C34.2, D13.1, J_AUDR.6, R52.1
/MIC_P: C33.2, D12.1, J_AUDR.5, R51.2
/MIPI0_C_N: J_CSI.8, U1.127 (MIPI0_C_N)
/MIPI0_C_P: J_CSI.9, U1.129 (MIPI0_C_P)
/MIPI0_D0_N: J_CSI.2, U1.115 (MIPI0_D0_N)
/MIPI0_D0_P: J_CSI.3, U1.117 (MIPI0_D0_P)
/MIPI0_D1_N: J_CSI.5, U1.121 (MIPI0_D1_N)
/MIPI0_D1_P: J_CSI.6, U1.123 (MIPI0_D1_P)
/MIPI1_C_N: J_DSI.8, U1.187 (MIPI1_C_N)
/MIPI1_C_P: J_DSI.9, U1.189 (MIPI1_C_P)
/MIPI1_D0_N: J_DSI.2, U1.175 (MIPI1_D0_N)
/MIPI1_D0_P: J_DSI.3, U1.177 (MIPI1_D0_P)
/MIPI1_D1_N: J_DSI.5, U1.181 (MIPI1_D1_N)
/MIPI1_D1_P: J_DSI.6, U1.183 (MIPI1_D1_P)
/MIPI1_D2_N: J_DSI.11, U1.193 (MIPI1_D2_N)
/MIPI1_D2_P: J_DSI.12, U1.195 (MIPI1_D2_P)
/MIPI1_D3_N: J_DSI.14, U1.194 (MIPI1_D3_N)
/MIPI1_D3_P: J_DSI.15, U1.196 (MIPI1_D3_P)
/PMIC_EN: D6.1 (C), R1.1, TP5.1, U1.99 (PMIC_ENABLE)
/PWR_BUT: D9.1 (C), D16.1 (K), J_KB.19
/RTC_3V0: C40.1, U1.76 (VBAT), U_RTC.2 (VOUT)
/RTC_VIN: C57.1, D37.1 (K), U_RTC.3 (VIN)
/SCL0: Q_I2C1.3 (D), U1.80 (SCL0)
/SCL0_PER: D33.5, D34.4, J_CSI.20, J_DSI.20, Q_I2C1.2 (S), R9.2
/SDA0: Q_I2C2.3 (D), U1.82 (SDA0)
/SDA0_PER: D33.4, D34.5, J_CSI.21, J_DSI.21, Q_I2C2.2 (S), R10.2
/SPKL_N: C61.1, FB2.2, J_SPKL.2
/SPKL_P: C60.1, FB1.2, J_SPKL.1
/SPKR_N: C63.1, FB4.2, J_SPKR.2
/SPKR_P: C62.1, FB3.2, J_SPKR.1
/TP_INT_N: D20.1, J_TP.5, R18.1, U1.50 (GPIO17)
/TP_RST_N: D21.1, J_TP.6, R19.1, U1.48 (GPIO27)
/TP_SCL: D23.1, J_TP.4, Q_TP1.2 (S), R82.2
/TP_SDA: D22.1, J_TP.3, Q_TP2.2 (S), R83.2
/USB2_N: TP3.1, U1.103 (USB2_N), U_ESD.3 (I/O2), U_ESD.4 (I/O2)
/USB2_P: TP2.1, U1.105 (USB2_P), U_ESD.1 (I/O1), U_ESD.6 (I/O1)
/USB3-0-D_N: J_USBL.11, U1.136 (USB3-0-D_N), U_ESD1.3 (I/O2), U_ESD1.4 (I/O2)
/USB3-0-D_P: J_USBL.10, U1.134 (USB3-0-D_P), U_ESD1.1 (I/O1), U_ESD1.6 (I/O1)
/USB3-1-D_N: J_USBL.14, U1.165 (USB3-1-D_N), U_ESD2.3 (I/O2), U_ESD2.4 (I/O2)
/USB3-1-D_P: J_USBL.13, U1.163 (USB3-1-D_P), U_ESD2.1 (I/O1), U_ESD2.6 (I/O1)
/USBL_J1_EN: D30.3, J_USBL.8, Q5.3 (D), R8.1, R91.2, U_VBUS.4 (EN)
/USBL_J1_FAULT_N: D29.5, J_USBL.4, R78.1, U1.30 (GPIO6)
/USBL_J1_UFP_N: D30.1, J_USBL.7, R79.1, U1.41 (GPIO25)
/USBL_PD_PG_N: D29.1, J_USBL.1, R75.1, U1.40 (GPIO9)
/USBL_U3_FLT_N: D29.3, J_USBL.2, R76.1, U1.44 (GPIO10)
/USBL_U5_FLT_N: D29.4, J_USBL.3, R77.1, U1.24 (GPIO26)
/USB_ISET: R31.1, U_VBUS.3 (ISET)
/USB_OTG_ID: R6.1, U1.101 (USB_OTG_ID)
/VBAT: C3.1, C69.1, D24.1 (C), D37.2 (A), F1.2, R50.1, U_CHG.22 (BAT), U_CHG.23 (BAT)
/VBAT_PACK: F1.1, J_BAT.1, J_BAT.2, J_BAT.3, J_BAT.4
/VBUS_ISET_HI: Q5.1 (G), Q6.1 (G), R90.2, U_UVLO.6 (OUTB)
/VBUS_PD: C2.1, D7.4 (VDD/IO), D7.5 (VDD/IO), D7.6 (VDD/IO), J5.1, J5.2, J5.3, J5.4, J5.5, Q3.3 (D), R60.1, R74.1
/VBUS_PD_SNUB: C58.1, R60.2
/VDD_1V8: C39.1, U1.88 (+1.8v_(Output)), U1.90 (+1.8v_(Output))
/VSYS: C5.1, C6.1, C10.1, C71.1, C72.1, C73.1, C74.1, C75.1, C76.1, C81.1, C82.1, C83.1, C93.1, F6.1, R33.1, R67.1, R88.1, U_BUCK.8 (VIN), U_BUCK2.8 (VIN), U_CHG.25 (SYS), U_UVLO.5 (VDD)
/VSYS_BL: C20.1, C92.1, L3.2, Q_BL.3 (D), U_BL.1 (VIN)
/VSYS_BL_SW: F6.2, Q_BL.2 (S), R35.2
/VSYS_THROT: R88.2, R89.1, R97.1, U_UVLO.4 (INB-)
/VSYS_THROT_HYS: Q6.3 (D), R97.2
/VSYS_UVLO: R33.2, R34.1, R81.2, U_UVLO.3 (INA+)
/WIFI_NDIS: R2.1, U1.89 (WiFi_nDisable)
/nRPIBOOT: D5.1, R4.1, SW1.1, SW1.2, TP6.1, U1.93 (nRPIBOOT)

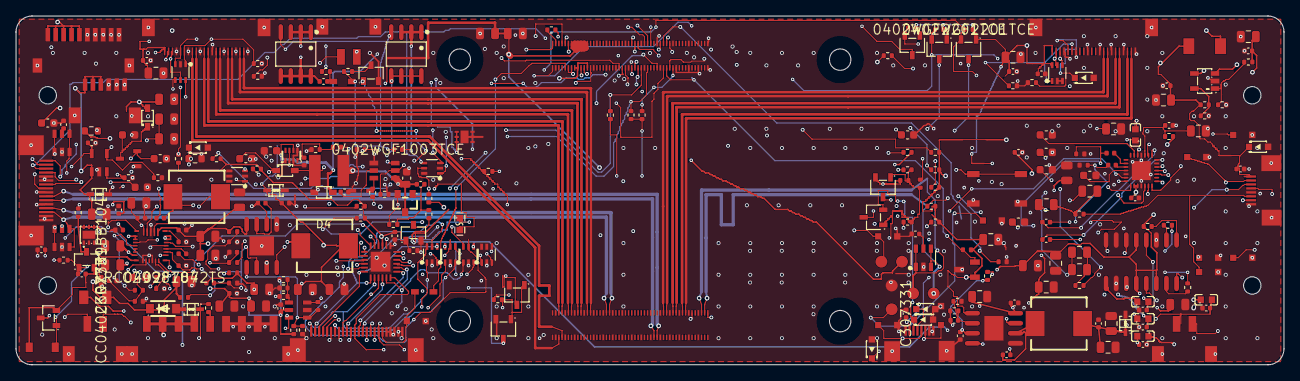
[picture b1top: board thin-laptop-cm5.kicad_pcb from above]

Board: 4 copper layers, 160.0 x 44.0 mm, 285 parts (0 on the bottom side), 186 nets.

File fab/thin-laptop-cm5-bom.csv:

Comment,Designator,Footprint,LCSC Part #
10uF,"C1,C3,C9,C19,C24,C35,C41,C43,C45,C47,C49,C65,C66,C67,C69,C71,C72,C73,C74,C75,C99",C_0805_2012Metric,C440198
100nF,"C2,C4,C10,C12,C16,C18,C23,C25,C36,C38,C42,C44,C46,C48,C50,C54,C59,C68,C76,C77,C80,C83,C87,C90,C91,C93,C95,C96,C97,C101",C_0402_1005Metric,C307331
220nF,"C21,C100",C_0402_1005Metric,C16772
1uF,"C11,C31,C32,C79",C_0402_1005Metric,C52923
47nF,"C7,C13",C_0402_1005Metric,C880605
22uF,"C5,C6,C14,C15,C55,C56,C64,C81,C82,C84,C85,C86",C_0805_2012Metric,C45783
22pF,"C17,C78",C_0402_1005Metric,C1555
10uF,C20,C_0603_1608Metric,C96446
1uF,C22,C_0603_1608Metric,C23829972
1uF,"C26,C27,C28,C37,C39,C40,C57,C58",C_0603_1608Metric,C15849
100uF,"C29,C30,C52,C53",C_0805_2012Metric,C141660
2.2uF,"C33,C34",C_0402_1005Metric,C159814
4.7uF,"C8,C51,C88",C_0603_1608Metric,C19666
1nF,"C60,C61,C62,C63",C_0402_1005Metric,C1523
1nF,C70,C_0402_1005Metric,C14442
470pF,C89,C_0402_1005Metric,C1537
10nF,"C92,C98",C_0402_1005Metric,C15195
B16WS,D1,SOD-323_L1.8-W1.3-LS2.5-RD,C364278
PESD5V0S1BA,"D10,D11,D12,D13",SOD-323_L1.7-W1.3-LS2.5-BI,C2827694
"PESD3V3U1UA,115","D5,D14,D20,D21,D22,D23,D31,D32,D40",SOD-323_L1.7-W1.3-LS2.5-RD,C403915
BZT52C12,D15,SOD-123_L2.7-W1.6-LS3.7-RD,C173429
1N4148WS,"D16,D37,D39",SOD-323_L1.8-W1.3-LS2.5-RD,C2128
PSD05-LF-T7,"D2,D18",SOD-323_L1.8-W1.3-LS2.5-RD,C139296
"PESD5V0S1UA,115","D4,D6,D9,D19",SOD-323_L1.8-W1.3-LS2.5-RD,C179414
SMF12A,D24,SOD-123F_L2.8-W1.8-LS3.7-RD,C123800
PESD3V3L5UY,"D25,D26,D27,D28,D29,D30,D33,D34",SOT-363_L2.0-W1.3-P0.65-LS2.1-BL,C2831531
TSD05CDYFR,D3,SOD-323_L1.8-W1.3-LS2.5-BI,C20611048
ESTVS3300DRVR,D35,DFN-6_L2.0-W2.0-P0.65-BL-EP1.6,C42400190
PESD36VS1UJX,D36,SOD-323F_L1.7-W1.3-LS2.5-RD,C5205187
BZT52C5V1S,D38,SOD-323_L1.8-W1.3-LS2.5-RD,C173436
ESTVS2200DRVR,D7,DFN-6_L2.0-W2.0-P0.65-BL-EP1.6,C42400188
8A,F1,F1206,C136353
1A,F6,F0603,C163118
BLM18PG121SN1D,"FB1,FB2,FB3,FB4,FB5",L0603,C14709
SM06B-SRSS-TB(LF)(SN),J4,CONN-SMD_SM06B-SRSS-TB-LF-SN,C160405
SM10B-SRSS-TB(LF)(SN),J5,CONN-SMD_10P-P1.00_SM10B-SRSS-TB-LF-SN,C160409
FPC-05F-8PH20,"J_AUDR,J_TP",FPC-SMD_8P-P0.50_FPC-05F-8PH20,C2856797
S9B-PH-SM4-TB(LF)(SN),J_BAT,CONN-SMD_9P-P2.50_S9B-PH-SM4-TB,C495694
S2B-PH-SM4-TB(LF)(SN),"J_BL,J_SPKL,J_SPKR",CONN-SMD_P2.00_S2B-PH-SM4-TB-LF-SN,C295747
FH12-22S-0.5SH(55),"J_CSI,J_DSI",FPC-SMD_22P-P0.50_FH12-22S-0.5SH-55,C597981
05A20L24P,J_KB,FPC-SMD_24P-P0.50_05A20L24P,C5362158
05B20U16P,J_USBL,FPC-SMD_16P-P0.50_05B20U16P,C18164516
2.2uH,"L1,L2,L5",IND-SMD_L7.0-W6.6,C167218
10uH,L3,IND-SMD_L4.0-W4.0_LQH44PN2R2MP0L,C135263
2.2uH,L4,IND-SMD_L4.5-W4.1_TMPC0412HP,C357134
AO4407A,"Q1,Q2",SOP-8_L5.0-W4.0-P1.27-LS6.0-BL,C2841482
SQ2318AES-T1_BE3,"Q3,Q4",SOT-23-3_L2.9-W1.3-P1.90-LS2.4-BR,C3280170
BSS138,"Q5,Q6,Q_CAM,Q_I2C1,Q_I2C2,Q_TP1,Q_TP2",SOT-23-3_L2.9-W1.6-P1.90-LS2.8-BR,C52895
AO3401A,Q_BL,SOT-23_L2.9-W1.3-P1.90-LS2.4-BR,C15127
2N7002,"Q_BL_EN,Q_DBG",SOT-23-3_L2.9-W1.3-P1.90-LS2.4-BR,C8545
10k,"R1,R2,R3,R4,R6,R13,R14,R15,R16,R17,R18,R19,R20,R21,R26,R37,R48,R54,R55,R56,R58,R59,R71,R75,R76,R77,R78,R79,R91,R93,R95",R_0402_1005Metric,C25744
2.2k,"R9,R10,R82,R83",R_0402_1005Metric,C25879
8.2k,R22,R_0603_1608Metric,C25981
5.23k,R23,R_0402_1005Metric,C11631
137k,R27,R_0402_1005Metric,C32298
24k,"R28,R65",R_0402_1005Metric,C25769
78.7k,R29,R_0402_1005Metric,C2998104
100k,"R8,R30,R35,R45,R46,R63,R66,R67,R80,R96,R97",R_0402_1005Metric,C25741
3.6k,R31,R_0402_1005Metric,C25891
1.5R,R32,R_0603_1608Metric,C22769
82k,R33,R_0402_1005Metric,C4142
5.1k,R34,R_0402_1005Metric,C25905
22R,"R36,R53",R_0402_1005Metric,C25092
30.1k,R42,R_0402_1005Metric,C29402
45.3k,R47,R_0402_1005Metric,C26980
4.7R,R49,R_0402_1005Metric,C25121
100R,"R50,R69,R87",R_0402_1005Metric,C25076
47k,"R51,R52,R68,R90",R_0402_1005Metric,C25792
2.2R,R60,R_0603_1608Metric,C22939
10R,"R61,R62,R74",R_0402_1005Metric,C25077
133k,R64,R_0402_1005Metric,C25753
30k,R7,R_0402_1005Metric,C25776
150k,"R72,R73",R_0402_1005Metric,C25755
1M,R81,R_0402_1005Metric,C26083
1k,R84,R_0402_1005Metric,C11702
80.6k,R88,R_0402_1005Metric,C25921
4.7k,R89,R_0402_1005Metric,C25900
22k,R94,R_0402_1005Metric,C25768
PTS526SM15SMTR2LFS,SW1,SW-SMD_4P-L5.2-W5.2-P3.70-LS6.4,C2689538
ComputeModule5-CM5,U1,Raspberry-Pi-5-Compute-Module,C597931
TLV62569DBVR,U_3V3,SOT-23-5_L3.0-W1.7-P0.95-LS2.8-BR,C141836
PAM8406DR,U_AMP,SOIC-16_L9.9-W3.9-P1.27-LS6.0-BL,C86270
TPS61165DBVR,U_BL,SOT-23-6_L2.9-W1.6-P0.95-LS2.8-BR,C58756
TPS56628DDAR,"U_BUCK,U_BUCK2",SOIC-8_L4.9-W3.9-P1.27-LS6.0-BL-EP,C485522
BQ25798RQMR,U_CHG,QFN-29_L4.0-W4.0-P0.40-TL-BQ25792RQMR,C2876593
ES8388,U_CODEC,QFN-28_L4.0-W4.0-P0.45-BL-EP,C365736
TPS2117DRLR,U_DBG,SOT-583-8_L2.1-W1.2-P0.50-LS1.6-BL,C22399676
USBLC6-2SC6,"U_ESD,U_ESD1,U_ESD2",SOT-23-6_L2.9-W1.6-P0.95-LS2.8-BL,C2687116
DRV5032FADBZR,U_HALL,SOT-23-3_L2.9-W1.3-P0.95-LS2.4-BR,C140921
TCA8418RTWR,U_KB,WQFN-24_L4.0-W4.0-P0.50-TL-EP2.5,C138713
HT7530S,U_RTC,SOT-23-3_L3.0-W1.7-P0.95-LS2.9-BR,C347214
TPS3700DDCR,U_UVLO,SOT-23-6_L2.9-W1.6-P0.95-LS2.8-BL,C33002
SY6280AAC,U_VBUS,SOT-23-5_L3.0-W1.7-P0.95-LS2.8-BL,C55136
